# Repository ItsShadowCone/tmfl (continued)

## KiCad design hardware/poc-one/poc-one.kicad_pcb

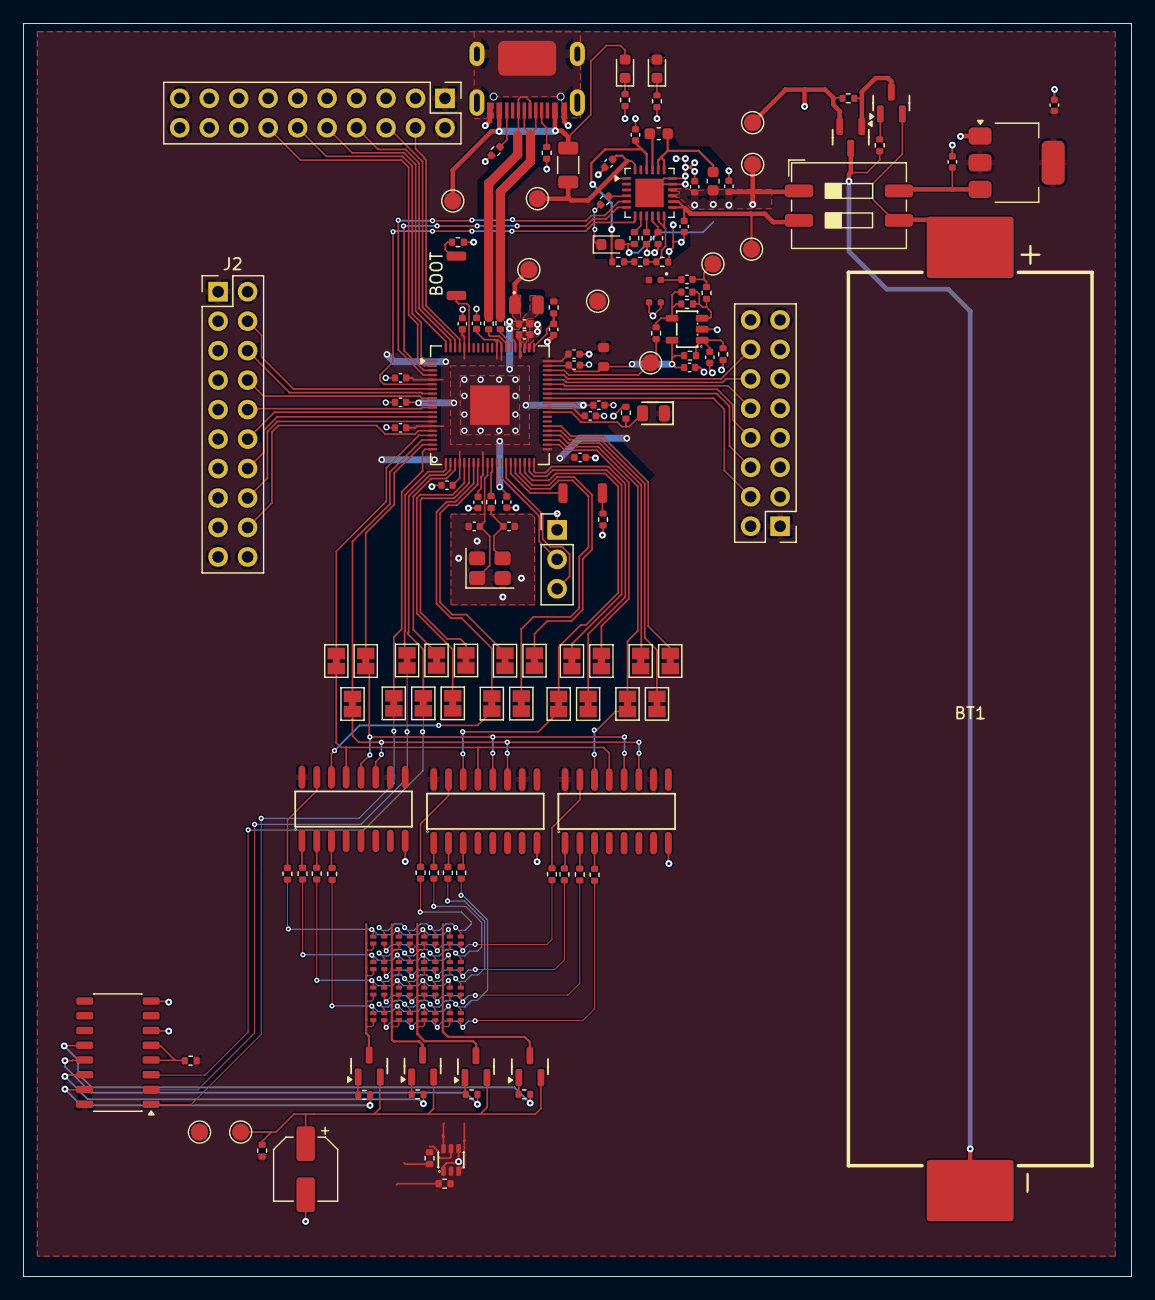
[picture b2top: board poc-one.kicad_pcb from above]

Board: 2 copper layers, 95.5 x 108.0 mm, 157 parts (0 on the bottom side), 140 nets.

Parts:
BT1: Battery_Cell; BH-18650-B6AA002
C1, C2: 15p; C_0402_1005Metric
C4, C5, C7, C8, C22: 4.7u; C_0402_1005Metric
C6, C9, C10, C11, C12, C13, C14, C15, C16, C17, C18, C38, C39: 100n; C_0402_1005Metric
C19: 1u; C_0402_1005Metric
C20: 47n; C_0603_1608Metric
C21, C23, C24, C25, C26, C35, C36: 10u; C_0402_1005Metric
C27: 100u; CP_Elec_5x5.4
C37: 100p; C_0402_1005Metric
D1, D2, D3: LED; LED_0603_1608Metric
D4, D5, D6, D7, D8, D9, D10, D11, D12, D13, D14, D15, D16, D17, D18, D19: LED_RABG; NH-B1212RGBA-HF
J1: MASTER_FANOUT; PinHeader_2x10_P2.54mm_Vertical
J2: SUBG_FANOUT; PinHeader_2x10_P2.54mm_Vertical
J3: Connector, USB-TYPE-C-16P; TYPE-C-SMD_HX-TYPE-C-16PIN
J4: TOUCH_FANOUT; PinHeader_2x08_P2.54mm_Vertical
J5: DEBUG; PinHeader_1x03_P2.54mm_Vertical
JP1, JP2, JP3, JP4, JP5, JP6, JP7, JP8, JP9, JP10, JP11, JP12, JP13, JP14, JP15, JP16, JP17, JP18, JP19, JP20, JP21: SolderJumper_2_Bridged; SolderJumper-2_P1.3mm_Bridged_Pad1.0x1.5mm
L1: 3.3u; AOTA-B201610S3R3-101-T
L2: 2u2; L_0603_1608Metric
MK1: LMA2718T421-OA5-2
Q1, Q3, Q4, Q5, Q6: SS8550 Y2 200-350; Q_SOT-23
Q2: 2N7002; Q_SOT-23
Q7: XYC-PT0805BC-L4-D; D_0805
R1: 0; R_0603
R3, R4, R6: 1k; R_0402_1005Metric
R5: 33; R_0402_1005Metric
R7, R8: 27; R_0402_1005Metric
R9: 330; R_0402_1005Metric
R10, R13: 2.2k; R_0402_1005Metric
R11, R12, R19: 5.1k; R_0402_1005Metric
R14: 100m; R_1206_3216Metric
R15, R16, R17, R21, R22, R23, R42, R43, R44: 10k; R_0402_1005Metric
R18, R24, R26, R26#2, R26#3, R27, R28: 220; R_0402_1005Metric
R20: 1.5k; R_0402_1005Metric
R25: 10; R_0402_1005Metric
R29, R30, R32, R35: 130; R_0402_1005Metric
R31, R34, R37, R39: 82; R_0402_1005Metric
R33, R36, R38, R40: 360; R_0402_1005Metric
R41: 2k; R_0402_1005Metric
R45: 100k; R_0402_1005Metric
R46: 100; R_0402_1005Metric
SW1, SW2: SW_Push; B3U-1100PM
SW3: BAT_SYS_PWR HY-DSIC02LS; SW_DIP_SPSTx02_Slide_9.78x7.26mm_W8.61mm_P2.54mm
TP1: VBUS; TestPoint_Pad_D1.5mm
TP2: +3V8 / VSYS; TestPoint_Pad_D1.5mm
TP3: +3V3; TestPoint_Pad_D1.5mm
TP4: VBUS-SENSE-; TestPoint_Pad_D1.5mm
TP5: +1V1; TestPoint_Pad_D1.5mm
TP6: GND; TestPoint_Pad_D1.5mm
TP7: VBAT; TestPoint_Pad_D1.5mm
TP8: DISPLAY_SENSE+; TestPoint_Pad_D1.5mm
TP9: DISPLAY_SENSE-; TestPoint_Pad_D1.5mm
TP10: MIC_RAW; TestPoint_Pad_D1.5mm
TP11: MIC_OUT; TestPoint_Pad_D1.5mm
U2: RP2354_80QFN; QFN-80-1EP_10x10mm_P0.4mm_EP3.4x3.4mm
U3: BQ24195LRGER; VQFN-24-1EP_4x4mm_P0.5mm_EP2.45x2.45mm
U4: NCP1117-3.3_SOT223; SOT-223-3_TabPin2
U6: 74HC138; JEITA_SOIC-16_3.9x9.9mm_P1.27mm
U10, U12, U14: 74HC595D; SOIC-16_L9.9-W3.9-P1.27-LS6.0-BL
U22: LMV321IDBVR; SOT-23-5_L3.0-W1.7-P0.95-LS2.8-BR
Y1: ABM8-272-T3; Crystal_SMD_3225-4Pin_3.2x2.5mm

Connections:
+1V1: C5.1, C6.1, C8.1, C9.1, L1.1, TP5.1 (1_1), U2.10 (DVDD), U2.32 (DVDD), U2.51 (DVDD), U2.65 (VREG_FB)
+3.3VADC: C11.2, C38.2, R1.2, R44.2, U2.59 (ADC_AVDD), U22.5 (V+)
+3V3: C4.1, C10.1, C12.1, C13.1, C14.1, C15.1, C16.1, C17.1, C18.1, C26.1, C39.1, D1.2 (A), J1.1, J1.2, J1.19, J1.20, J2.1, J2.2, J2.19, J2.20, J4.1, J4.2, J4.15, J4.16, MK1.4 (VDD), Q7.1 (C), R1.1, R5.1, R23.1, R25.1, TP3.1 (1_1), TP8.1 (1_1), U2.5 (IOVDD), U2.15 (IOVDD), U2.24 (IOVDD), U2.29 (IOVDD), U2.41 (IOVDD), U2.50 (IOVDD), U2.60 (IOVDD), U2.64 (VREG_VIN), U2.68 (USB_OTP_VDD), U2.69 (QSPI_IOVDD), U2.76 (IOVDD), U4.2 (VO), U6.16 (VCC), U10.10 (MR#), U10.16 (VCC), U12.10 (MR#), U12.16 (VCC), U14.10 (MR#), U14.16 (VCC)
+3V8: C23.2, C24.2, D3.2 (A), L2.2, R15.1, SW3.1, TP2.1 (1_1), U3.15 (SYS), U3.16 (SYS)
/Analog/AMB_LIGHT_OUT: Q7.2 (E), R42.1, U2.49 (GPIO40_ADC0)
/Analog/MIC_OUT: R46.1, TP11.1 (1_1), U2.58 (GPIO47_ADC7)
/Analog/TOUCH1: J4.4, U2.52 (GPIO41_ADC1)
/Analog/TOUCH2: J4.6, U2.53 (GPIO42_ADC2)
/Analog/TOUCH3: J4.8, U2.54 (GPIO43_ADC3)
/Analog/TOUCH4: J4.10, U2.55 (GPIO44_ADC4)
/Analog/TOUCH5: J4.12, U2.56 (GPIO45_ADC5)
/Analog/TOUCH6: J4.14, U2.57 (GPIO46_ADC6)
/BOOTSEL: SW1.2, U2.75 (QSPI_SS)
/Battery/INT: U2.6 (GPIO8), U3.7 (INT)
/Battery/SCL: U2.4 (GPIO7), U3.5 (SCL)
/Battery/SDA: U2.3 (GPIO6), U3.6 (SDA)
/Battery/USB_D+: J3.A6 (D+), J3.B6 (D+), R7.1
/Battery/USB_D-: J3.A7 (D-), J3.B7 (D-), R8.1
/GPIO9: J2.4, U2.7 (GPIO9)
/GPIO14: J2.14, U2.13 (GPIO14)
/GPIO15: J2.16, U2.14 (GPIO15)
/GPIO16: J2.18, U2.16 (GPIO16)
/LED_control/CLK: JP2.2 (B), U10.11 (SHCP), U12.11 (SHCP), U14.11 (SHCP)
/LED_control/C_P_1: JP4.2 (B), U6.1 (A0)
/LED_control/C_P_2: JP5.2 (B), U6.2 (A1)
/LED_control/C_P_3: JP6.2 (B), U6.3 (A2)
/LED_control/LED_matrix/+0: D4.2 (A), D8.2 (A), D12.2 (A), D16.2 (A), Q3.3 (C)
/LED_control/LED_matrix/+1: D5.2 (A), D9.2 (A), D13.2 (A), D17.2 (A), Q4.3 (C)
/LED_control/LED_matrix/+2: D6.2 (A), D10.2 (A), D14.2 (A), D18.2 (A), Q5.3 (C)
/LED_control/LED_matrix/+3: D7.2 (A), D11.2 (A), D15.2 (A), D19.2 (A), Q6.3 (C)
/LED_control/LED_matrix/B0: D4.3 (BK), D5.3 (BK), D6.3 (BK), D7.3 (BK), R31.1
/LED_control/LED_matrix/B1: D8.3 (BK), D9.3 (BK), D10.3 (BK), D11.3 (BK), R34.1
/LED_control/LED_matrix/B2: D12.3 (BK), D13.3 (BK), D14.3 (BK), D15.3 (BK), R37.1
/LED_control/LED_matrix/B3: D16.3 (BK), D17.3 (BK), D18.3 (BK), D19.3 (BK), R39.1
/LED_control/LED_matrix/G0: D4.4 (GK), D5.4 (GK), D6.4 (GK), D7.4 (GK), R33.1
/LED_control/LED_matrix/G1: D8.4 (GK), D9.4 (GK), D10.4 (GK), D11.4 (GK), R36.1
/LED_control/LED_matrix/G2: D12.4 (GK), D13.4 (GK), D14.4 (GK), D15.4 (GK), R38.1
/LED_control/LED_matrix/G3: D16.4 (GK), D17.4 (GK), D18.4 (GK), D19.4 (GK), R40.1
/LED_control/LED_matrix/R0: D4.1 (RK), D5.1 (RK), D6.1 (RK), D7.1 (RK), R29.1
/LED_control/LED_matrix/R1: D8.1 (RK), D9.1 (RK), D10.1 (RK), D11.1 (RK), R30.1
/LED_control/LED_matrix/R2: D12.1 (RK), D13.1 (RK), D14.1 (RK), D15.1 (RK), R32.1
/LED_control/LED_matrix/R3: D16.1 (RK), D17.1 (RK), D18.1 (RK), D19.1 (RK), R35.1
/LED_control/R_S_1_B: JP18.2 (B), U14.14 (DS)
/LED_control/R_S_1_G: JP14.2 (B), U12.14 (DS)
/LED_control/R_S_1_R: JP10.2 (B), U10.14 (DS)
/LED_control/STOP: JP3.2 (B), U10.12 (STCP), U12.12 (STCP), U14.12 (STCP)
/LED_control/~OE: JP1.2 (B), U10.13 (OE#), U12.13 (OE#), U14.13 (OE#)
/M-CIPO: J1.12, U2.1 (GPIO4)
/M-COPI: J1.10, U2.80 (GPIO3)
/M-CS: J1.14, U2.2 (GPIO5)
/M-RX: J1.4, U2.77 (GPIO0)
/M-SCK: J1.8, U2.79 (GPIO2)
/M-TX: J1.6, U2.78 (GPIO1)
/RESET: SW2.2, U2.35 (RUN)
/SUBG_CIPO: J2.10, U2.11 (GPIO12)
/SUBG_COPI: J2.8, U2.9 (GPIO11)
/SUBG_CS: J2.12, U2.12 (GPIO13)
/SUBG_SCK: J2.6, U2.8 (GPIO10)
GND: C1.2, C2.2, C4.2, C5.2, C6.2, C7.2, C8.2, C9.2, C10.2, C11.1, C12.2, C13.2, C14.2, C15.2, C16.2, C17.2, C18.2, C19.2, C21.2, C22.2, C23.1, C24.1, C25.2, C26.2, C27.2, C36.2, C38.1, C39.2, J1.3, J1.5, J1.7, J1.9, J1.11, J1.13, J1.15, J1.16, J1.17, J1.18, J2.3, J2.5, J2.7, J2.9, J2.11, J2.13, J2.15, J2.17, J3.A12B1 (GND), J3.B12A1 (GND), J3.S1 (SHIELD), J4.3, J4.5, J4.7, J4.9, J4.11, J4.13, J5.1, MK1.2 (GND), MK1.3 (GND), Q2.2 (S), R4.2, R6.2, R9.1, R10.1, R11.2, R12.2, R16.2, R17.2, R18.2, R21.2, R42.2, R43.1, TP6.1 (1_1), U2.62 (VREG_PGND), U2.81 (GND), U3.17 (PGND), U3.18 (PGND), U3.25 (Thermal), U4.1 (GND), U6.6 (E2), U6.8 (GND), U10.8 (GND), U12.8 (GND), U14.8 (GND), U22.2 (GND), Y1.2 (G), Y1.4 (G)
unnamed: BT1.1 (+), Q1.2 (E), SW3.3
unnamed: BT1.2 (-), Q2.3 (D), R22.2
unnamed: C2.1, R3.2, Y1.3
unnamed: C19.1, R14.2, TP4.1 (1_1), U3.1 (VBUS), U3.24 (VBUS)
unnamed: C20.2, L2.1, U3.19 (SW), U3.20 (SW)
unnamed: C21.1, SW3.2, TP7.1 (1_1), U3.13 (BAT), U3.14 (BAT)
unnamed: C35.2, R41.2, TP10.1 (1_1)
unnamed: D1.1 (K), R9.2
unnamed: D2.1 (K), R10.2
unnamed: D3.1 (K), R13.2
unnamed: J3.A5 (CC1), R12.1
unnamed: J3.B5 (CC2), R11.1
unnamed: J5.2, U2.33 (SWCLK)
unnamed: J5.3, U2.34 (SWD)
unnamed: JP1.1 (A), U2.17 (GPIO17)
unnamed: JP2.1 (A), U2.18 (GPIO18)
unnamed: JP3.1 (A), U2.19 (GPIO19)
unnamed: JP4.1 (A), U2.20 (GPIO20)
unnamed: JP5.1 (A), U2.21 (GPIO21)
unnamed: JP6.1 (A), U2.22 (GPIO22)
unnamed: JP7.1 (A), U2.23 (GPIO23)
unnamed: JP8.1 (A), U2.25 (GPIO24)
unnamed: JP9.1 (A), U2.26 (GPIO25)
unnamed: JP10.1 (A), U2.27 (GPIO26)
unnamed: JP11.1 (A), U2.28 (GPIO27)
unnamed: JP12.1 (A), U2.36 (GPIO28)
unnamed: JP13.1 (A), U2.37 (GPIO29)
unnamed: JP14.1 (A), U2.38 (GPIO30)
unnamed: JP15.1 (A), U2.39 (GPIO31)
unnamed: JP16.1 (A), U2.40 (GPIO32)
unnamed: JP17.1 (A), U2.42 (GPIO33)
unnamed: JP18.1 (A), U2.43 (GPIO34)
unnamed: JP19.1 (A), U2.44 (GPIO35)
unnamed: JP20.1 (A), U2.45 (GPIO36)
unnamed: JP21.1 (A), U2.46 (GPIO37)
unnamed: C35.1, MK1.1 (OUT)
unnamed: Q1.1 (B), R22.1
unnamed: Q1.3 (C), Q2.1 (G), R21.1
unnamed: Q3.1 (B), R24.2
unnamed: C27.1, Q3.2 (E), Q4.2 (E), Q5.2 (E), Q6.2 (E), R25.2, TP9.1 (1_1)
unnamed: Q4.1 (B), R26#3.2
unnamed: Q5.1 (B), R27.2
unnamed: Q6.1 (B), R28.2
unnamed: R4.1, SW2.1
unnamed: R6.1, SW1.1
unnamed: R19.2, R20.1
unnamed: R8.2, U2.66 (USB_DM)
unnamed: R7.2, U2.67 (USB_DP)
unnamed: C7.1, R5.2, U2.61 (VREG_AVDD)
unnamed: L1.2, U2.63 (VREG_LX)
unnamed: C1.1, U2.30 (XIN), Y1.1
unnamed: R3.1, U2.31 (XOUT)
unnamed: C20.1, U3.21 (BTST)
unnamed: R18.1, U3.10 (ILIM)
unnamed: R15.2, U3.8 (OTG)
unnamed: C22.1, R19.1, U3.22 (REGN)
unnamed: R13.1, U3.4 (STAT)
unnamed: R17.1, R20.2, U3.11 (TS1), U3.12 (TS2)
unnamed: R16.1, U3.9 (~CE)
unnamed: C25.1, SW3.4, U4.3 (VI)
unnamed: R23.2, U6.4 (~E0), U6.5 (~E1)
unnamed: R24.1, U6.15 (~Y0)
unnamed: R26#3.1, U6.14 (~Y1)
unnamed: R27.1, U6.13 (~Y2)
unnamed: R28.1, U6.12 (~Y3)
unnamed: R29.2, U10.15 (Q0)
unnamed: R30.2, U10.1 (Q1)
unnamed: R32.2, U10.2 (Q2)
unnamed: R35.2, U10.3 (Q3)
unnamed: R33.2, U12.15 (Q0)
unnamed: R36.2, U12.1 (Q1)
unnamed: R38.2, U12.2 (Q2)
unnamed: R40.2, U12.3 (Q3)
unnamed: R31.2, U14.15 (Q0)
unnamed: R34.2, U14.1 (Q1)
unnamed: R37.2, U14.2 (Q2)
unnamed: R39.2, U14.3 (Q3)
unnamed: C36.1, R43.2, R44.1, U22.1 (+)
unnamed: C37.2, R41.1, R45.2, U22.3 (-)
unnamed: C37.1, R45.1, R46.2, U22.4 (OUT)
VBUS: D2.2 (A), J3.A9B4 (VBUS), J3.B9A4 (VBUS), R14.1, TP1.1 (1_1)

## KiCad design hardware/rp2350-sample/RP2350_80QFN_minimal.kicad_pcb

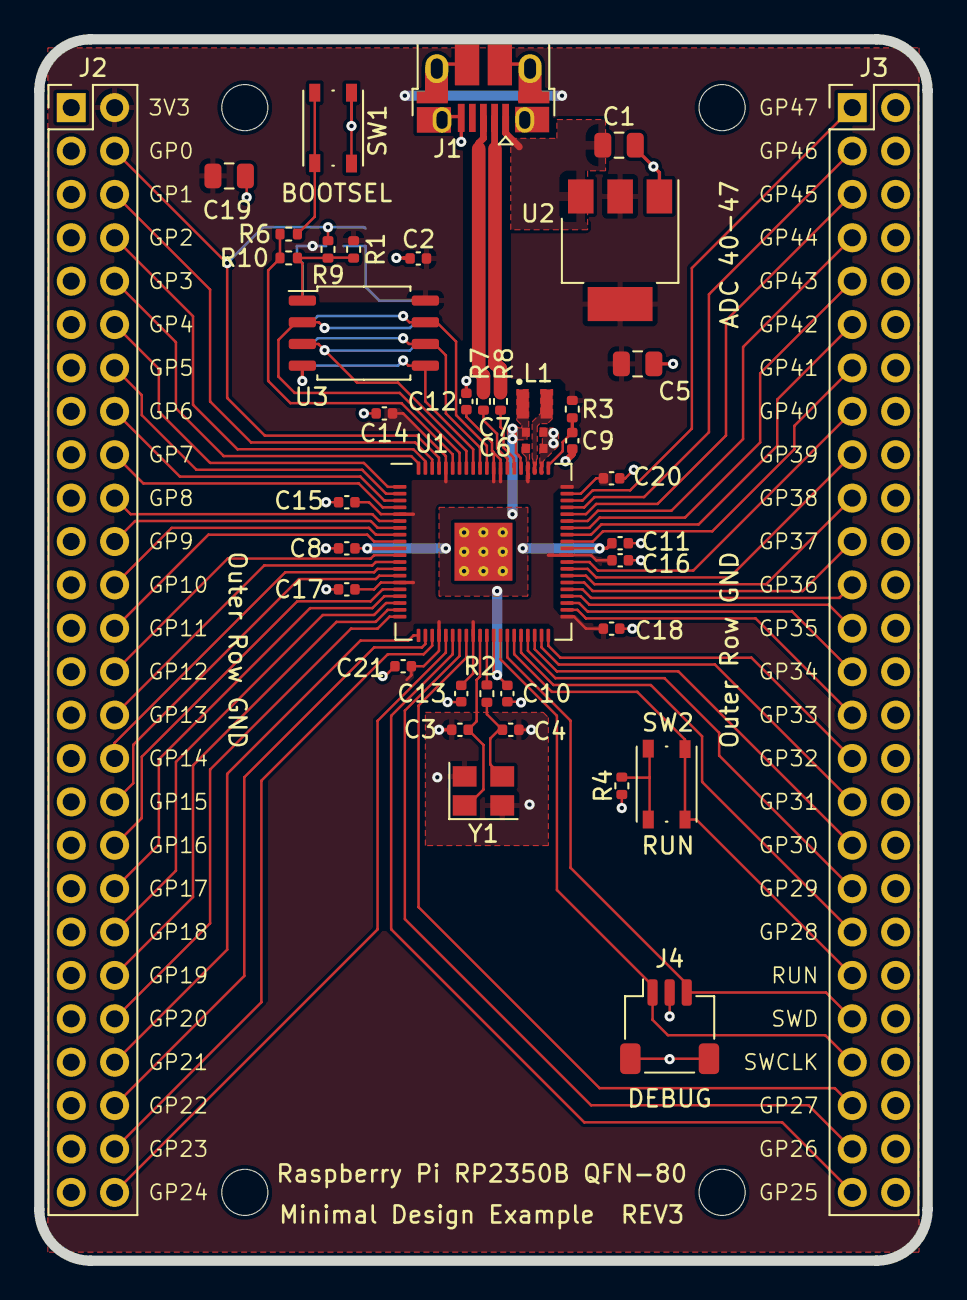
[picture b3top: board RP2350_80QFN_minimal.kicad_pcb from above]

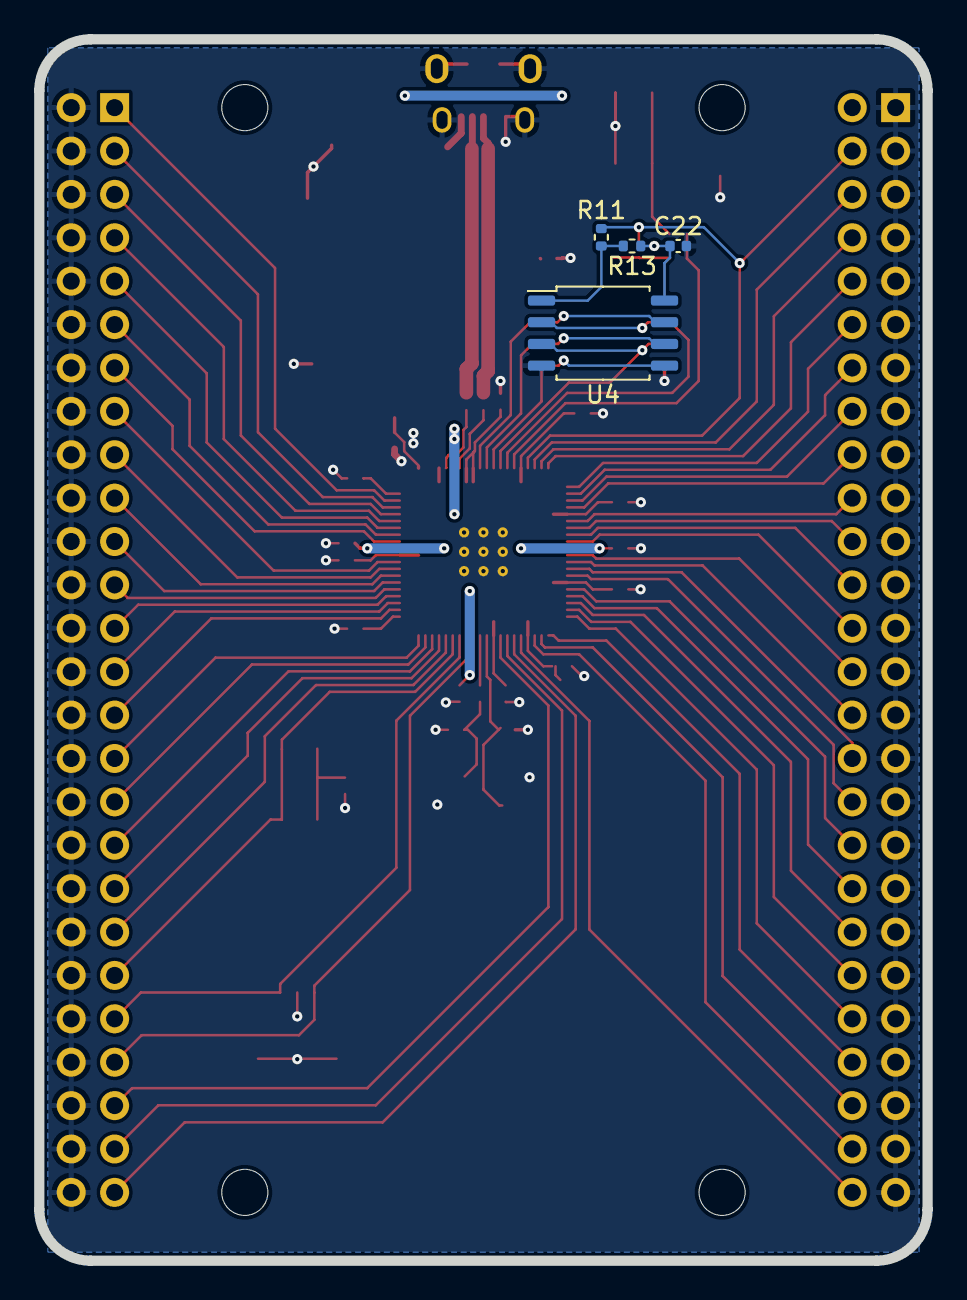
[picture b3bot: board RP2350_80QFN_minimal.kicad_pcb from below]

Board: 2 copper layers, 52.0 x 71.5 mm, 49 parts (4 on the bottom side), 74 nets.

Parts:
C1, C5, C19: 10u; C_0805_2012Metric
C2, C8, C11, C12, C13, C14, C15, C16, C17, C18, C20, C21: 100n; C_0402_1005Metric
C3, C4: 15p; C_0402_1005Metric
C6, C7: 4.7u; C_0402_1005Metric_small_pads
C9, C10: 4.7u; C_0402_1005Metric
C22: DNF; C_0402_1005Metric
H1, H2, H3, H4: MountingHole; MountingHole_2.7mm_M2.5
J1: USB_B_Micro; USB_Micro-B_Amphenol_10103594-0001LF_Horizontal
J2, J3: Conn_02x26_Odd_Even; PinHeader_2x26_P2.54mm_Vertical
J4: SM03B-SRSS-TB; JST_SH_SM03B-SRSS-TB_1x03-1MP_P1.00mm_Horizontal
L1: 3.3u; L_pol_2016
R1, R9, R11, R13: DNF; R_0402_1005Metric
R2, R4, R6: 1k; R_0402_1005Metric
R3: 33; R_0402_1005Metric
R7, R8: 27; R_0402_1005Metric
R10: 0; R_0402_1005Metric
SW1, SW2: SW_Push; SW_Push_1P1T_NO_Vertical_Wuerth_434133025816
U1: RP2350_80QFN; RP2350-QFN-80-1EP_10x10_P0.4mm_EP3.4x3.4mm_ThermalVias
U2: NCP1117-3.3_SOT223; SOT-223-3_TabPin2
U3: W25Q128JVS; SOIC-8_5.23x5.23mm_P1.27mm
U4: DNF; SOIC-8_5.23x5.23mm_P1.27mm
Y1: ABM8-272-T3; Crystal_SMD_3225-4Pin_3.2x2.5mm

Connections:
+1V1: C7.1, C8.1, C10.1, C11.1, L1.1, U1.10 (DVDD), U1.32 (DVDD), U1.51 (DVDD), U1.65 (VREG_FB)
+3V3: C2.1, C5.1, C6.1, C12.1, C13.1, C14.1, C15.1, C16.1, C17.1, C18.1, C19.1, C20.1, C21.1, C22.1, J2.2, R1.1, R3.1, R13.1, U1.5 (IOVDD), U1.15 (IOVDD), U1.24 (IOVDD), U1.29 (IOVDD), U1.41 (IOVDD), U1.50 (IOVDD), U1.59 (ADC_AVDD), U1.60 (IOVDD), U1.64 (VREG_VIN), U1.68 (USB_OTP_VDD), U1.69 (QSPI_IOVDD), U1.76 (IOVDD), U2.2 (VO), U3.8 (VCC), U4.8 (VCC)
/FLASH2_SS: R11.2, R13.2, U4.1 (~CS)
/FLASH_SS: R1.2, R9.2, R10.2, U3.1 (~CS)
/GPIO0: J2.4, R9.1, R11.1, U1.77 (GPIO0)
/GPIO1: J2.6, U1.78 (GPIO1)
/GPIO2: J2.8, U1.79 (GPIO2)
/GPIO3: J2.10, U1.80 (GPIO3)
/GPIO4: J2.12, U1.1 (GPIO4)
/GPIO5: J2.14, U1.2 (GPIO5)
/GPIO6: J2.16, U1.3 (GPIO6)
/GPIO7: J2.18, U1.4 (GPIO7)
/GPIO8: J2.20, U1.6 (GPIO8)
/GPIO9: J2.22, U1.7 (GPIO9)
/GPIO10: J2.24, U1.8 (GPIO10)
/GPIO11: J2.26, U1.9 (GPIO11)
/GPIO12: J2.28, U1.11 (GPIO12)
/GPIO13: J2.30, U1.12 (GPIO13)
/GPIO14: J2.32, U1.13 (GPIO14)
/GPIO15: J2.34, U1.14 (GPIO15)
/GPIO16: J2.36, U1.16 (GPIO16)
/GPIO17: J2.38, U1.17 (GPIO17)
/GPIO18: J2.40, U1.18 (GPIO18)
/GPIO19: J2.42, U1.19 (GPIO19)
/GPIO20: J2.44, U1.20 (GPIO20)
/GPIO21: J2.46, U1.21 (GPIO21)
/GPIO22: J2.48, U1.22 (GPIO22)
/GPIO23: J2.50, U1.23 (GPIO23)
/GPIO24: J2.52, U1.25 (GPIO24)
/GPIO25: J3.51, U1.26 (GPIO25)
/GPIO26: J3.49, U1.27 (GPIO26)
/GPIO27: J3.47, U1.28 (GPIO27)
/GPIO28: J3.39, U1.36 (GPIO28)
/GPIO29: J3.37, U1.37 (GPIO29)
/GPIO30: J3.35, U1.38 (GPIO30)
/GPIO31: J3.33, U1.39 (GPIO31)
/GPIO32: J3.31, U1.40 (GPIO32)
/GPIO33: J3.29, U1.42 (GPIO33)
/GPIO34: J3.27, U1.43 (GPIO34)
/GPIO35: J3.25, U1.44 (GPIO35)
/GPIO36: J3.23, U1.45 (GPIO36)
/GPIO37: J3.21, U1.46 (GPIO37)
/GPIO38: J3.19, U1.47 (GPIO38)
/GPIO39: J3.17, U1.48 (GPIO39)
/GPIO40_ADC0: J3.15, U1.49 (GPIO40_ADC0)
/GPIO41_ADC1: J3.13, U1.52 (GPIO41_ADC1)
/GPIO42_ADC2: J3.11, U1.53 (GPIO42_ADC2)
/GPIO43_ADC3: J3.9, U1.54 (GPIO43_ADC3)
/GPIO44_ADC4: J3.7, U1.55 (GPIO44_ADC4)
/GPIO45_ADC5: J3.5, U1.56 (GPIO45_ADC5)
/GPIO46_ADC6: J3.3, U1.57 (GPIO46_ADC6)
/GPIO47_ADC7: J3.1, U1.58 (GPIO47_ADC7)
/QSPI_SCLK: U1.71 (QSPI_SCLK), U3.6 (CLK), U4.6 (CLK)
/QSPI_SD0: U1.72 (QSPI_SD0), U3.5 (DI(IO0)), U4.5 (DI(IO0))
/QSPI_SD1: U1.74 (QSPI_SD1), U3.2 (DO(IO1)), U4.2 (DO(IO1))
/QSPI_SD2: U1.73 (QSPI_SD2), U3.3 (IO2), U4.3 (IO2)
/QSPI_SD3: U1.70 (QSPI_SD3), U3.7 (IO3), U4.7 (IO3)
/QSPI_SS: R6.1, R10.1, U1.75 (QSPI_SS)
/RUN: J3.41, SW2.2, U1.35 (RUN)
/SWCLK: J3.45, J4.1, U1.33 (SWCLK)
/SWD: J3.43, J4.3, U1.34 (SWD)
/USB_D+: J1.3 (D+), R7.1
/USB_D-: J1.2 (D-), R8.1
/VREG_AVDD: C9.1, R3.2, U1.61 (VREG_AVDD)
/VREG_LX: L1.2, U1.63 (VREG_LX)
/XIN: C3.1, U1.30 (XIN), Y1.1
/XOUT: R2.1, U1.31 (XOUT)
/~USB_BOOT: R6.2, SW1.2
GND: C1.2, C2.2, C3.2, C4.2, C5.2, C6.2, C7.2, C8.2, C9.2, C10.2, C11.2, C12.2, C13.2, C14.2, C15.2, C16.2, C17.2, C18.2, C19.2, C20.2, C21.2, C22.2, J1.5 (GND), J1.6 (Shield), J2.1, J2.3, J2.5, J2.7, J2.9, J2.11, J2.13, J2.15, J2.17, J2.19, J2.21, J2.23, J2.25, J2.27, J2.29, J2.31, J2.33, J2.35, J2.37, J2.39, J2.41, J2.43, J2.45, J2.47, J2.49, J2.51, J3.2, J3.4, J3.6, J3.8, J3.10, J3.12, J3.14, J3.16, J3.18, J3.20, J3.22, J3.24, J3.26, J3.28, J3.30, J3.32, J3.34, J3.36, J3.38, J3.40, J3.42, J3.44, J3.46, J3.48, J3.50, J3.52, J4.2, J4.MP (MountPin), R4.2, SW1.1, U1.62 (VREG_PGND), U1.81 (GND), U2.1 (GND), U3.4 (GND), U4.4 (GND), Y1.2, Y1.4
unnamed: C4.1, R2.2, Y1.3
unnamed: R4.1, SW2.1
unnamed: R8.2, U1.66 (USB_DM)
unnamed: R7.2, U1.67 (USB_DP)
VBUS: C1.1, J1.1 (VBUS), U2.3 (VI)

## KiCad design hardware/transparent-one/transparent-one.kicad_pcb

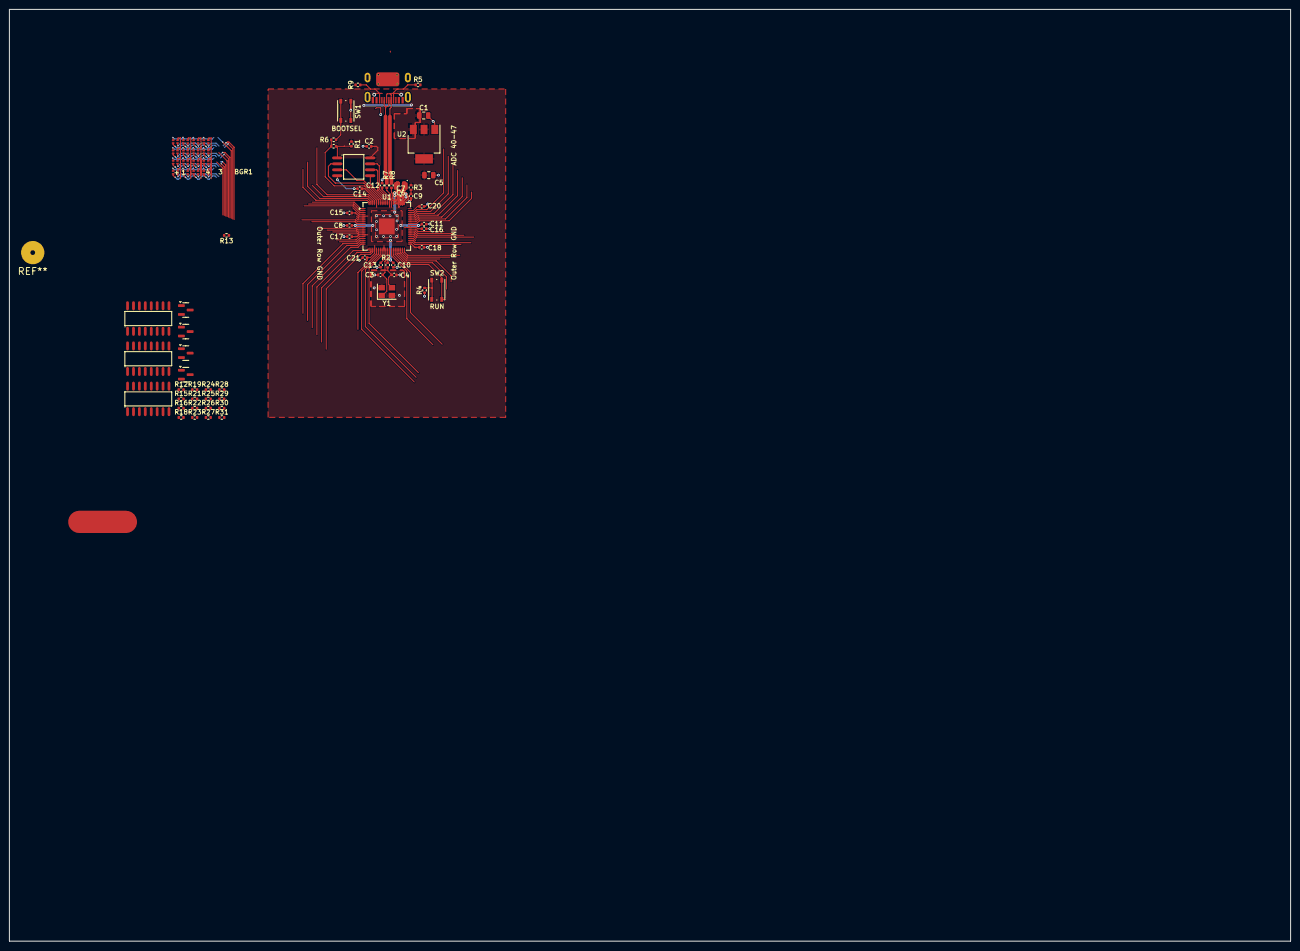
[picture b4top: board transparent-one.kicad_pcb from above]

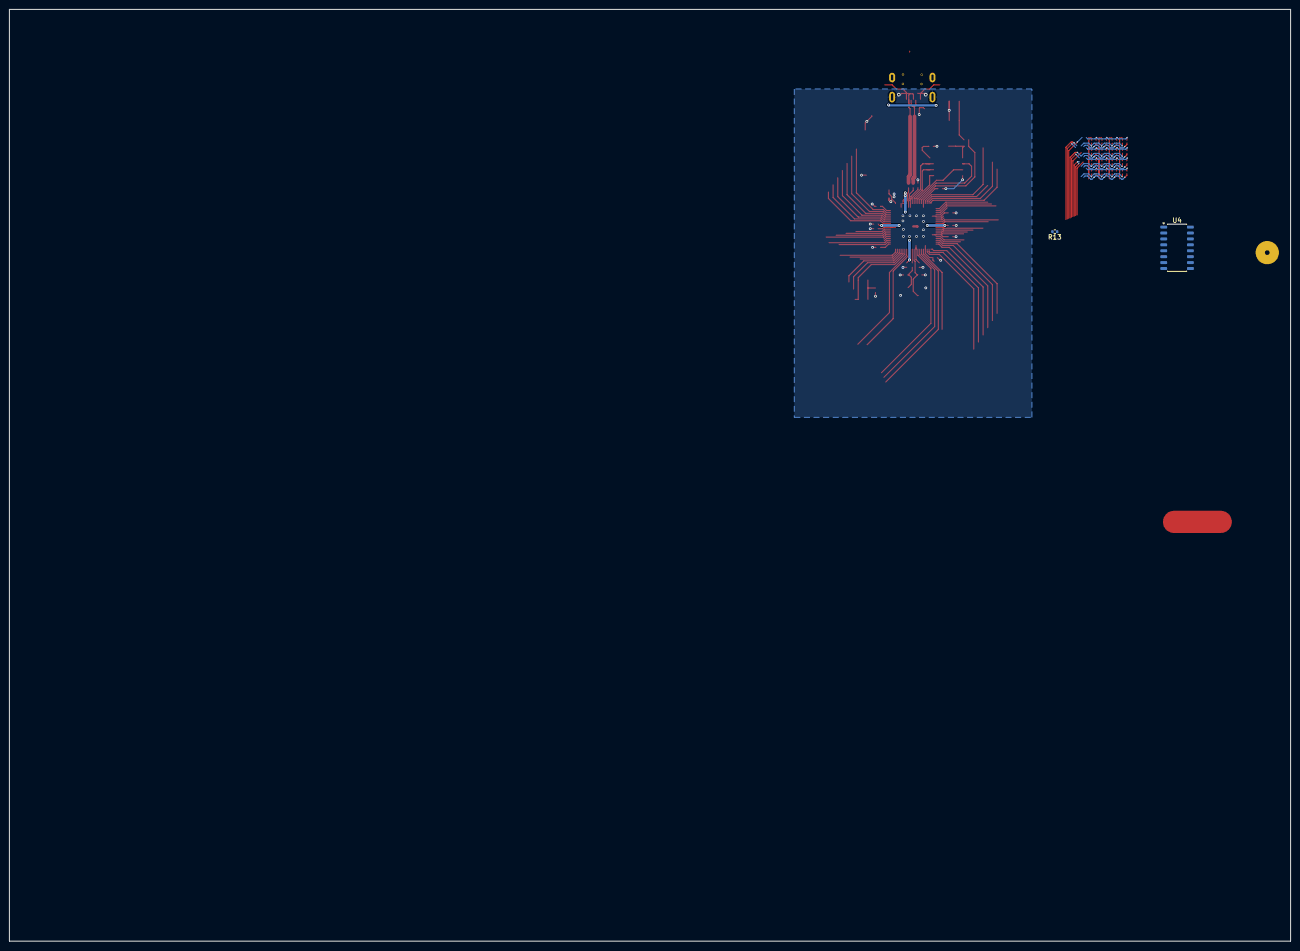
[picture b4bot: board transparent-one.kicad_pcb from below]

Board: 2 copper layers, 275.0 x 200.0 mm, 80 parts (2 on the bottom side), 71 nets.

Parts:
C1, C5: 10u; C_0805_2012Metric
C2, C8, C11, C12, C13, C14, C15, C16, C17, C18, C20, C21: 100n; C_0402_1005Metric
C3, C4: 15p; C_0402_1005Metric
C6, C7, C9, C10: 4.7u; C_0402_1005Metric
D1, D2, D3, D4, D5, D6, D7, D8, D9, D10, D11, D12, D13, D14, D15, D16: LED_RABG; NH-B1212RGBA-HF
J4: Connector, USB-TYPE-C-16P; TYPE-C-SMD_HX-TYPE-C-16PIN
L1: 3.3u; AOTA-B201610S3R3-101-T
Q1, Q2, Q3, Q5: SS8550 Y2 200-350; Q_SOT-23
R1: DNF; R_0402_1005Metric
R2, R4, R6: 1k; R_0402_1005Metric
R3: 33; R_0402_1005Metric
R5, R9: 5.1k; R_0402_1005Metric
R7, R8: 27; R_0402_1005Metric
R10, R23: 0; R_0402_1005Metric
R12, R15, R18, R21: 82; R_0402_1005Metric
R13, R13#2, R16, R19, R22: 360; R_0402_1005Metric
R24, R25, R26, R27: 220; R_0402_1005Metric
R28, R29, R30, R31: 130; R_0402_1005Metric
SW1, SW2: SW_Push; SW_Push_1P1T_NO_Vertical_Wuerth_434133025816
U1: RP2350_80QFN; QFN-80-1EP_10x10mm_P0.4mm_EP3.4x3.4mm
U2: NCP1117-3.3_SOT223; SOT-223-3_TabPin2
U3: W25Q128; SOIC-8_L5.3-W5.3-P1.27-LS8.0-BL
U4: 74HC138; JEITA_SOIC-16_3.9x9.9mm_P1.27mm
U9, U11, U13: 74HC595D; SOIC-16_L9.9-W3.9-P1.27-LS6.0-BL
Y1: ABM8-272-T3; Crystal_SMD_3225-4Pin_3.2x2.5mm

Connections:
+1V1: C7.1, C8.1, C10.1, C11.1, L1.1, U1.10 (DVDD), U1.32 (DVDD), U1.51 (DVDD), U1.65 (VREG_FB)
+3V3: C2.1, C5.1, C6.1, C12.1, C13.1, C14.1, C15.1, C16.1, C17.1, C18.1, C20.1, C21.1, Q1.2 (E), Q2.2 (E), Q3.2 (E), Q5.2 (E), R1.1, R3.1, R23.1, U1.5 (IOVDD), U1.15 (IOVDD), U1.24 (IOVDD), U1.29 (IOVDD), U1.41 (IOVDD), U1.50 (IOVDD), U1.59 (ADC_AVDD), U1.60 (IOVDD), U1.64 (VREG_VIN), U1.68 (USB_OTP_VDD), U1.69 (QSPI_IOVDD), U1.76 (IOVDD), U2.2 (VO), U3.8 (VCC), U4.16 (VCC), U9.10 (MR#), U9.16 (VCC), U11.10 (MR#), U11.16 (VCC), U13.10 (MR#), U13.16 (VCC)
/FLASH_SS: R1.2, R10.2, U3.1 (CS#)
/GPIO0: U1.77 (GPIO0), U9.13 (OE#), U11.13 (OE#), U13.13 (OE#)
/GPIO1: U1.78 (GPIO1), U9.11 (SHCP), U11.11 (SHCP), U13.11 (SHCP)
/GPIO2: U1.79 (GPIO2), U9.12 (STCP), U11.12 (STCP), U13.12 (STCP)
/GPIO3: U1.80 (GPIO3), U4.1 (A0)
/GPIO4: U1.1 (GPIO4), U4.2 (A1)
/GPIO5: U1.2 (GPIO5), U4.3 (A2)
/GPIO9: U1.7 (GPIO9), U9.14 (DS)
/GPIO13: U1.12 (GPIO13), U11.14 (DS)
/GPIO17: U1.17 (GPIO17), U13.14 (DS)
/LED_control/LED_matrix/+0: D1.2 (A), D5.2 (A), D9.2 (A), D13.2 (A), Q5.3 (C)
/LED_control/LED_matrix/+1: D2.2 (A), D6.2 (A), D10.2 (A), D14.2 (A), Q1.3 (C)
/LED_control/LED_matrix/+2: D3.2 (A), D7.2 (A), D11.2 (A), D15.2 (A), Q2.3 (C)
/LED_control/LED_matrix/+3: D4.2 (A), D8.2 (A), D12.2 (A), D16.2 (A), Q3.3 (C)
/LED_control/LED_matrix/B0: D1.3 (BK), D2.3 (BK), D3.3 (BK), D4.3 (BK), R12.1
/LED_control/LED_matrix/B1: D5.3 (BK), D6.3 (BK), D7.3 (BK), D8.3 (BK), R15.1
/LED_control/LED_matrix/B2: D9.3 (BK), D10.3 (BK), D11.3 (BK), D12.3 (BK), R18.1
/LED_control/LED_matrix/B3: D13.3 (BK), D14.3 (BK), D15.3 (BK), D16.3 (BK), R21.1
/LED_control/LED_matrix/G0: D1.4 (GK), D2.4 (GK), D3.4 (GK), D4.4 (GK), R13.1, R13#2.1
/LED_control/LED_matrix/G1: D5.4 (GK), D6.4 (GK), D7.4 (GK), D8.4 (GK), R16.1
/LED_control/LED_matrix/G2: D9.4 (GK), D10.4 (GK), D11.4 (GK), D12.4 (GK), R19.1
/LED_control/LED_matrix/G3: D13.4 (GK), D14.4 (GK), D15.4 (GK), D16.4 (GK), R22.1
/LED_control/LED_matrix/R0: D1.1 (RK), D2.1 (RK), D3.1 (RK), D4.1 (RK), R28.1
/LED_control/LED_matrix/R1: D5.1 (RK), D6.1 (RK), D7.1 (RK), D8.1 (RK), R29.1
/LED_control/LED_matrix/R2: D9.1 (RK), D10.1 (RK), D11.1 (RK), D12.1 (RK), R30.1
/LED_control/LED_matrix/R3: D13.1 (RK), D14.1 (RK), D15.1 (RK), D16.1 (RK), R31.1
/QSPI_SCLK: U1.71 (QSPI_SCLK), U3.6 (CLK)
/QSPI_SD0: U1.72 (QSPI_SD0), U3.5 (DI)
/QSPI_SD1: U1.74 (QSPI_SD1), U3.2 (DO)
/QSPI_SD2: U1.73 (QSPI_SD2), U3.3 (IO2)
/QSPI_SD3: U1.70 (QSPI_SD3), U3.7 (IO3)
/QSPI_SS: R6.1, R10.1, U1.75 (QSPI_SS)
/RUN: SW2.2, U1.35 (RUN)
/USB_D+: J4.A6 (D+), J4.B6 (D+), R7.1
/USB_D-: J4.A7 (D-), J4.B7 (D-), R8.1
/VREG_AVDD: C9.1, R3.2, U1.61 (VREG_AVDD)
/VREG_LX: L1.2, U1.63 (VREG_LX)
/XIN: C3.1, U1.30 (XIN), Y1.1
/XOUT: R2.1, U1.31 (XOUT)
/~USB_BOOT: R6.2, SW1.2
GND: C1.2, C2.2, C3.2, C4.2, C5.2, C6.2, C7.2, C8.2, C9.2, C10.2, C11.2, C12.2, C13.2, C14.2, C15.2, C16.2, C17.2, C18.2, C20.2, C21.2, J4.A12B1 (GND), J4.B12A1 (GND), J4.S1 (SHIELD), R4.2, R5.2, R9.2, SW1.1, U1.62 (VREG_PGND), U1.81 (GND), U2.1 (GND), U3.4 (GND), U4.6 (E2), U4.8 (GND), U9.8 (GND), U11.8 (GND), U13.8 (GND), Y1.2, Y1.4
unnamed: C4.1, R2.2, Y1.3
unnamed: J4.A5 (CC1), R5.1
unnamed: J4.B5 (CC2), R9.1
unnamed: Q1.1 (B), R25.2
unnamed: Q2.1 (B), R26.2
unnamed: Q3.1 (B), R27.2
unnamed: Q5.1 (B), R24.2
unnamed: R4.1, SW2.1
unnamed: R8.2, U1.66 (USB_DM)
unnamed: R7.2, U1.67 (USB_DP)
unnamed: R23.2, U4.4 (~E0), U4.5 (~E1)
unnamed: R24.1, U4.15 (~Y0)
unnamed: R25.1, U4.14 (~Y1)
unnamed: R26.1, U4.13 (~Y2)
unnamed: R27.1, U4.12 (~Y3)
unnamed: R28.2, U9.15 (Q0)
unnamed: R29.2, U9.1 (Q1)
unnamed: R30.2, U9.2 (Q2)
unnamed: R31.2, U9.3 (Q3)
unnamed: R13.2, R13#2.2, U11.15 (Q0)
unnamed: R16.2, U11.1 (Q1)
unnamed: R19.2, U11.2 (Q2)
unnamed: R22.2, U11.3 (Q3)
unnamed: R12.2, U13.15 (Q0)
unnamed: R15.2, U13.1 (Q1)
unnamed: R18.2, U13.2 (Q2)
unnamed: R21.2, U13.3 (Q3)
VBUS: C1.1, J4.A9B4 (VBUS), J4.B9A4 (VBUS), U2.3 (VI)

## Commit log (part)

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2026-04-23 initial_commit
2026-04-27 schematic-v2
2026-04-27 poc-one update & bom
2026-04-30 fixed a couple resistors, reworked footprints incl. datasheets
2026-05-01 poc-one routed & schematic changes
2026-05-07 added stuff
2026-06-24 bom changes for poc-two
